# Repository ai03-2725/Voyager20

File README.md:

# Voyager20-3700
A versatile, modern numpad PCB

This is the 3700 variant for the Cherry G80-3700.
For the regular variant, see [this](https://github.com/ai03-2725/Voyager20).

#### In light of recent claims that I am 100% liable for any of my open source PCBs, I am adding this disclaimer.
#### I provide these PCBs as a reference for designing keyboard PCBs. Using them within your projects will require a will to do research of one's own and to learn the workings of them, potentially fixing issues if they exist.
# I provide these PCBs without liability and without any guarantees regarding functionality, as expressed in the MIT license under which all of these PCBs are licensed.

### Features
* In-switch LED backlighting
* Jumper to switch numlock key between numlock indicator and regular backlight
* 2U positions can be replaced with 2x1U keys
* Over-current and static discharge protection
* Fully open-source
* Note: This variant does not have USB Type-C or RGB underglow for obvious reasons.

### The Voyager PCB Family
The Voyager PCBs offer fully featured PCBs fit for any keyboard, whether mass production or high-end.

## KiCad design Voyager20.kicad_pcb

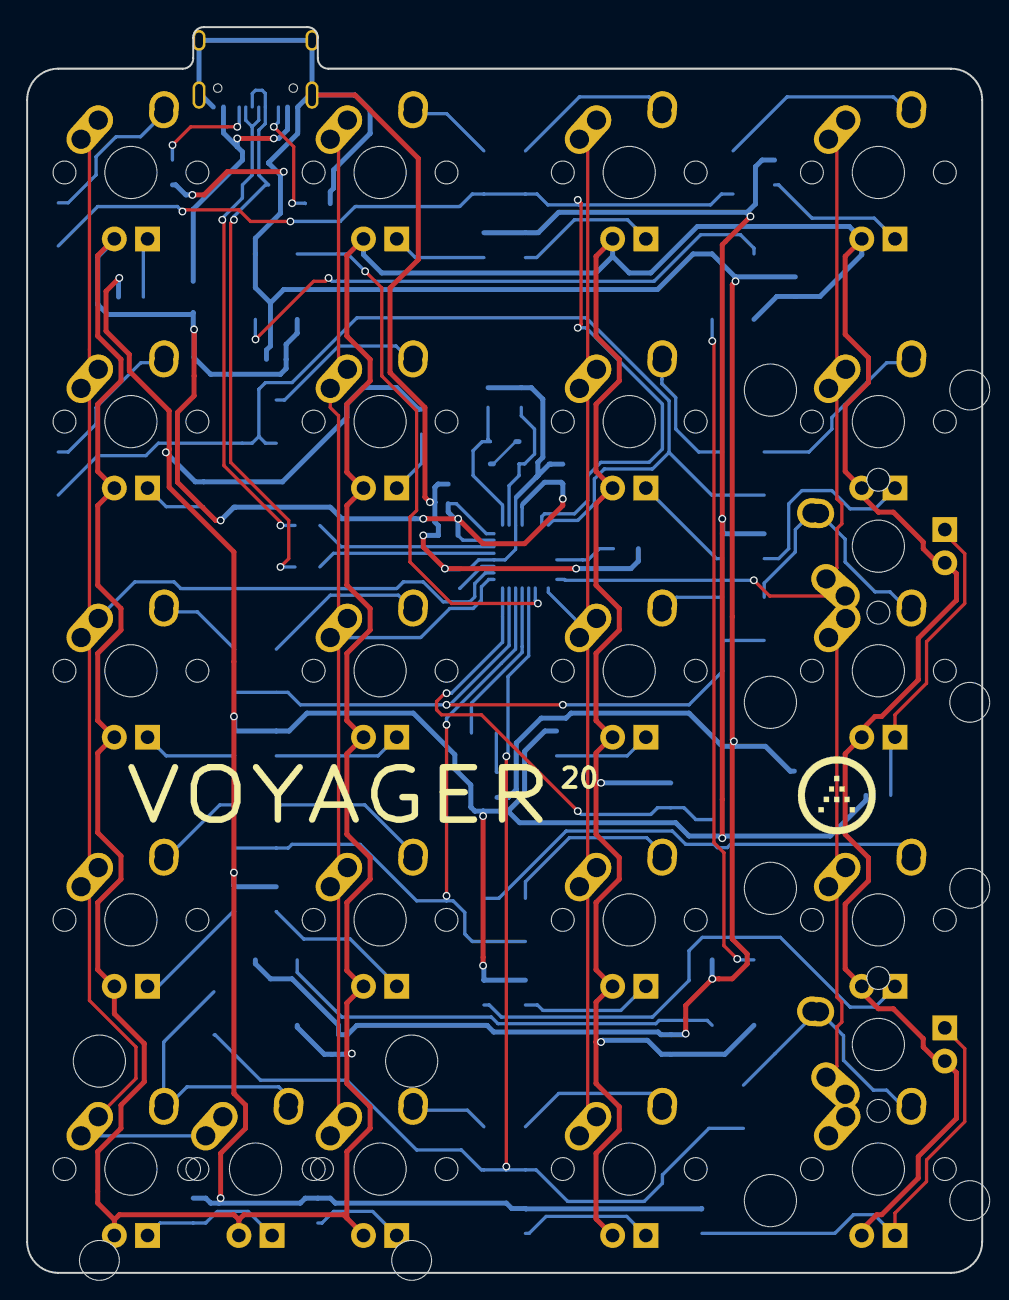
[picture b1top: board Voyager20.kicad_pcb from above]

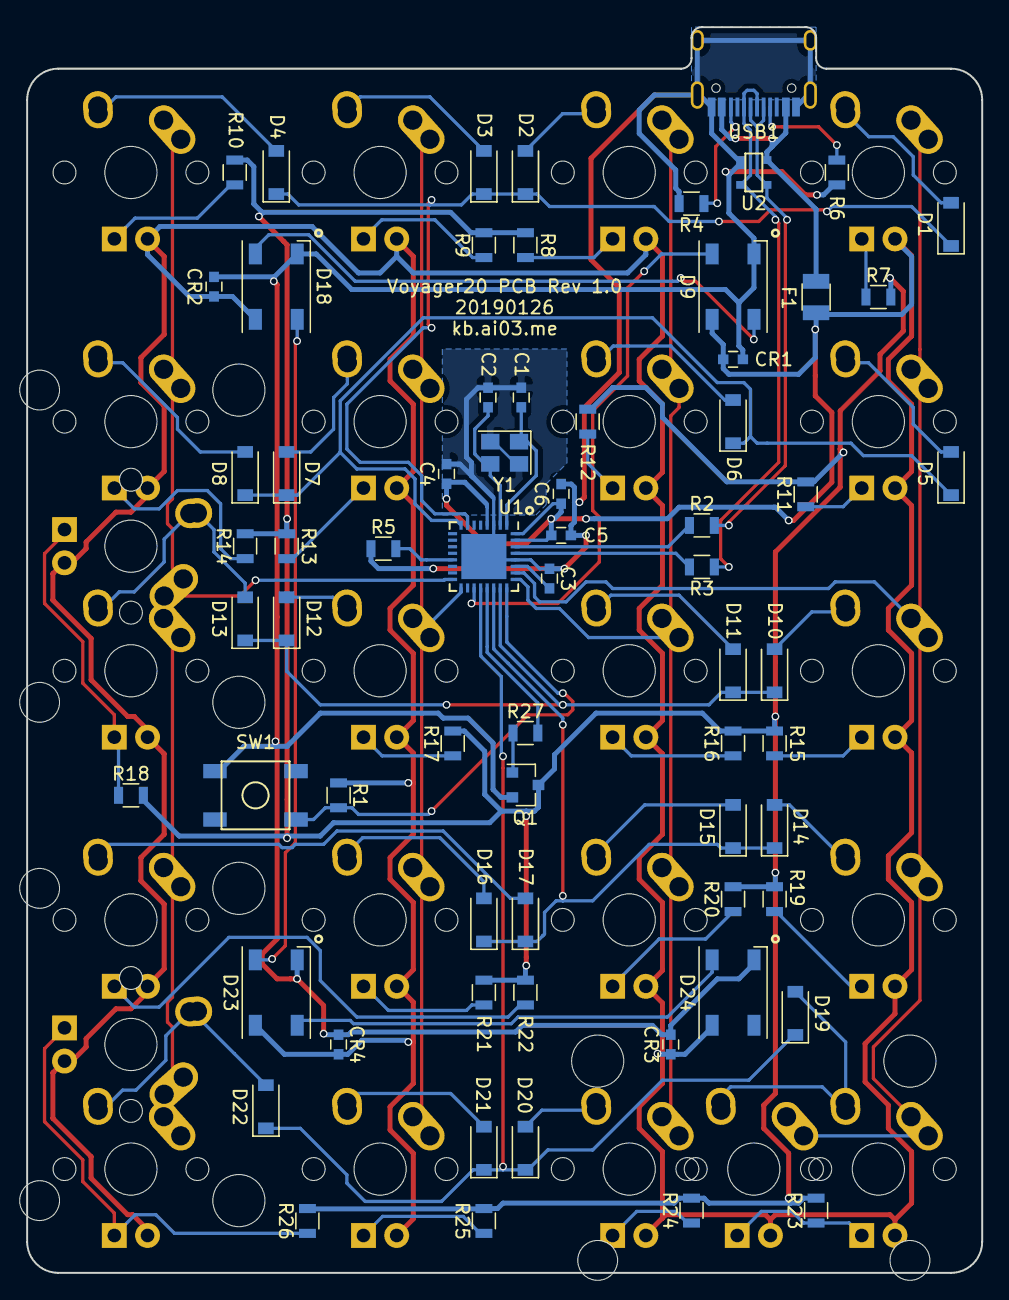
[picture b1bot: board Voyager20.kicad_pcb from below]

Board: 2 copper layers, 73.0 x 95.2 mm, 91 parts (68 on the bottom side), 70 nets.

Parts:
C1, C2: 22p; C_0603
C3: 1uF; C_0603
C4, C5: 0.1u; C_0603
C6: 4.7u; C_0603
CR1, CR2, CR3, CR4: 0.1u; C_0603
D1, D2, D3, D4, D5, D6, D7, D8, D10, D11, D12, D13, D14, D15, D16, D17, D19, D20, D21, D22: SOD-123; D_SOD-123
D9, D18, D23, D24: WS2812B; LED_WS2812B-PLCC4
F1: 500mA; Fuse_SMD1206_Reflow
MX1, MX2, MX3, MX4, MX5, MX6, MX7, MX8, MX9, MX10, MX11, MX12, MX13, MX14, MX15, MX16, MX17, MX18, MX19, MX20: MX-1U
MX-E-1, MX-E-2, MX-E-3: MX-2U; MX-2U-ReversedStabilizers
Q1: Q_NPN_BEC; SOT-23
R1, R5: 10k; R_0805
R2, R3: 22; R_0805
R4, R6: 5.1k; R_0805
R7, R8, R9, R10, R11, R12, R13, R14, R15, R16, R17, R18, R19, R20, R21, R22, R23, R24, R25, R26, R27: 1k; R_0805
SW1: SW_Push; SKQG-1155865
U1: ATmega32U2-AU; QFN-32-1EP_5x5mm_Pitch0.5mm
U2: PRTR5V0U2X; SOT143B
USB1: HRO-TYPE-C-31-M-12; HRO-TYPE-C-31-M-12-Assembly
Y1: 16MHz; Crystal_SMD_3225-4pin_3.2x2.5mm

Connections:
+5V: C4.1, C5.1, C6.1, CR1.1, CR2.1, CR3.1, CR4.1, D9.1, D18.1, D23.1, D24.1, F1.1, MX1.3, MX2.3, MX3.3, MX4.3, MX5.3, MX6.3, MX7.3, MX8.3, MX9.3, MX10.3, MX11.3, MX12.3, MX13.3, MX14.3, MX15.3, MX16.3, MX17.3, MX18.3, MX19.3, MX20.3, MX-E-1.3, MX-E-2.3, MX-E-3.3, R1.1, U1.4, U1.31, U1.32
COL0: MX1.1, MX5.1, MX9.1, MX13.1, MX17.1, MX-E-3.1, U1.26
COL1: MX2.1, MX6.1, MX10.1, MX14.1, MX18.1, U1.25
COL2: MX3.1, MX7.1, MX11.1, MX15.1, MX19.1, U1.17
COL3: MX4.1, MX8.1, MX12.1, MX16.1, MX20.1, MX-E-1.1, MX-E-2.1, U1.16
D+: R3.2, U1.29
D-: R2.1, U1.30
GND: C1.2, C2.2, C3.2, C4.2, C5.2, C6.2, CR1.2, CR2.2, CR3.2, CR4.2, D9.3, D18.3, D23.3, D24.3, Q1.2, R4.2, R5.1, R6.2, SW1.1, U1.3, U1.28, U2.1, USB1.1, USB1.12, USB1.13, Y1.2, Y1.4
LEDGND: Q1.3, R7.2, R8.2, R9.2, R10.2, R11.2, R12.2, R13.2, R14.2, R15.2, R16.2, R17.2, R18.2, R19.2, R20.2, R21.2, R22.2, R23.2, R24.2, R25.2, R26.2
unnamed: C1.1, U1.1, Y1.1
unnamed: C2.1, U1.2, Y1.3
unnamed: C3.1, U1.27
unnamed: D1.2, MX1.2
unnamed: D2.2, MX2.2
unnamed: D3.2, MX3.2
unnamed: D4.2, MX4.2
unnamed: D5.2, MX5.2
unnamed: D6.2, MX6.2
unnamed: D7.2, MX7.2
unnamed: D8.2, MX8.2
unnamed: D10.2, MX9.2
unnamed: D11.2, MX10.2
unnamed: D12.2, MX11.2
unnamed: D13.2, MX12.2, MX-E-1.2
unnamed: D14.2, MX13.2
unnamed: D15.2, MX14.2
unnamed: D16.2, MX15.2
unnamed: D17.2, MX16.2
unnamed: D18.2, D23.4
unnamed: D9.2, D18.4
unnamed: D19.2, MX17.2, MX-E-3.2
unnamed: D20.2, MX18.2
unnamed: D21.2, MX19.2
unnamed: D22.2, MX20.2, MX-E-2.2
unnamed: D23.2, D24.4
unnamed: MX1.4, R7.1
unnamed: MX2.4, R8.1
unnamed: MX3.4, R9.1
unnamed: MX4.4, R10.1
unnamed: MX5.4, R11.1
unnamed: MX6.4, R12.1
unnamed: MX7.4, R13.1
unnamed: MX8.4, R14.1
unnamed: MX9.4, R15.1
unnamed: MX10.4, R16.1
unnamed: MX11.4, R17.1
unnamed: MX13.4, R19.1
unnamed: MX14.4, R20.1
unnamed: MX15.4, R21.1
unnamed: MX16.4, R22.1
unnamed: MX18.4, R24.1
unnamed: MX19.4, R25.1
unnamed: MX12.4, MX-E-1.4, R18.1
unnamed: MX20.4, MX-E-2.4, R26.1
unnamed: MX17.4, MX-E-3.4, R23.1
unnamed: Q1.1, R27.1
unnamed: R1.2, SW1.2, U1.24
unnamed: R2.2, U2.3, USB1.5, USB1.7
unnamed: R3.1, U2.2, USB1.6, USB1.8
unnamed: R4.1, USB1.10
unnamed: R5.2, U1.13
unnamed: R6.1, USB1.4
unnamed: R27.2, U1.21
RGBLED: D9.4, U1.19
ROW0: D1.1, D2.1, D3.1, D4.1, U1.7
ROW1: D5.1, D6.1, D7.1, D8.1, U1.8
ROW2: D10.1, D11.1, D12.1, D13.1, U1.23
ROW3: D14.1, D15.1, D16.1, D17.1, U1.22
ROW4: D19.1, D20.1, D21.1, D22.1, U1.20
VCC: F1.2, U2.4, USB1.2, USB1.11

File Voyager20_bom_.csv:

Component,Description,Part,References,Value,Footprint,Quantity Per PCB,Datasheet
1,Unpolarized capacitor,C_Small,C4 C5 CR1 CR2 CR3 CR4,0.1u,C_0603,6,
2,Unpolarized capacitor,C_Small,C3,1uF,C_0603,1,
3,Unpolarized capacitor,C_Small,C1 C2,22p,C_0603,2,
4,Unpolarized capacitor,C_Small,C6,4.7u,C_0603,1,
5,"Diode, small symbol",D_Small,D1 D2 D3 D4 D5 D6 D7 D8 D10 D11 D12 D13 D14 D15 D16 D17 D19 D20 D21 D22,SOD-123,D_SOD-123,20,~
6,RGB LED with integrated controller,WS2812B,D9 D18 D23 D24,WS2812B,LED_WS2812B-PLCC4,4,https://cdn-shop.adafruit.com/datasheets/WS2812B.pdf
7,"resettable fuse, polymeric positive temperature coefficient (PPTC), small symbol",Polyfuse_Small,F1,500mA,Fuse_SMD1206_Reflow,1,
8,,MX-1U,MX1 MX2 MX3 MX4 MX5 MX6 MX7 MX8 MX9 MX10 MX11 MX12 MX13 MX14 MX15 MX16 MX17 MX18 MX19 MX20,MX-1U,MX-1U,20,
9,,MX-1U,MX-E-1 MX-E-2 MX-E-3,MX-2U,MX-2U-ReversedStabilizers,3,
10,Transistor NPN (general),Q_NPN_BEC,Q1,Q_NPN_BEC,SOT-23,1,~
11,"Resistor, small symbol",R_Small,R1 R5,10k,R_0805,2,
12,"Resistor, small symbol",R_Small,R7 R8 R9 R10 R11 R12 R13 R14 R15 R16 R17 R18 R19 R20 R21 R22 R23 R24 R25 R26 R27,1k,R_0805,21,~
13,"Resistor, small symbol",R_Small,R2 R3,22,R_0805,2,
14,"Resistor, small symbol",R_Small,R4 R6,5.1k,R_0805,2,
15,"Push button switch, generic, two pins",SW_Push,SW1,SW_Push,SKQG-1155865,1,
16,"16MHz, 8kB Flash, 512B SRAM, 512B EEPROM, TQFP-32",ATmega32U2-AU,U1,ATmega32U2-AU,QFN-32-1EP_5x5mm_Pitch0.5mm,1,http://ww1.microchip.com/downloads/en/DeviceDoc/doc7799.pdf
17,,PRTR5V0U2X,U2,PRTR5V0U2X,SOT143B,1,
18,,HRO-TYPE-C-31-M-12,USB1,HRO-TYPE-C-31-M-12,HRO-TYPE-C-31-M-12-Assembly,1,
19,"Four pin crystal, two ground/package pins (pin2 and 4) small symbol",Crystal_GND24_Small,Y1,16MHz,Crystal_SMD_3225-4pin_3.2x2.5mm,1,





Component Groups:,19
Component Count:,91
Fitted Components:,91
Number of PCBs:,1
Total components:,91
Schematic Version:,
Schematic Date:,
BoM Date:,2/17/2019 7:45:39 PM
Schematic Source:,C:\Users\Ryota\Documents\GitHub\Voyager20\Voyager20.sch
KiCad Version:,Eeschema (5.0.0)

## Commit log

2019-01-25 Add submods
2019-01-25 Build schem
2019-01-27 Build numpad
2019-01-27 Make 24 key variant
2019-02-05 Route 3700 variant
2019-02-05 Tweak a trace
2019-02-05 Major revision
2019-02-18 Voyager20 update
2019-02-18 Make BOM
2019-02-18 Generate generic bom
